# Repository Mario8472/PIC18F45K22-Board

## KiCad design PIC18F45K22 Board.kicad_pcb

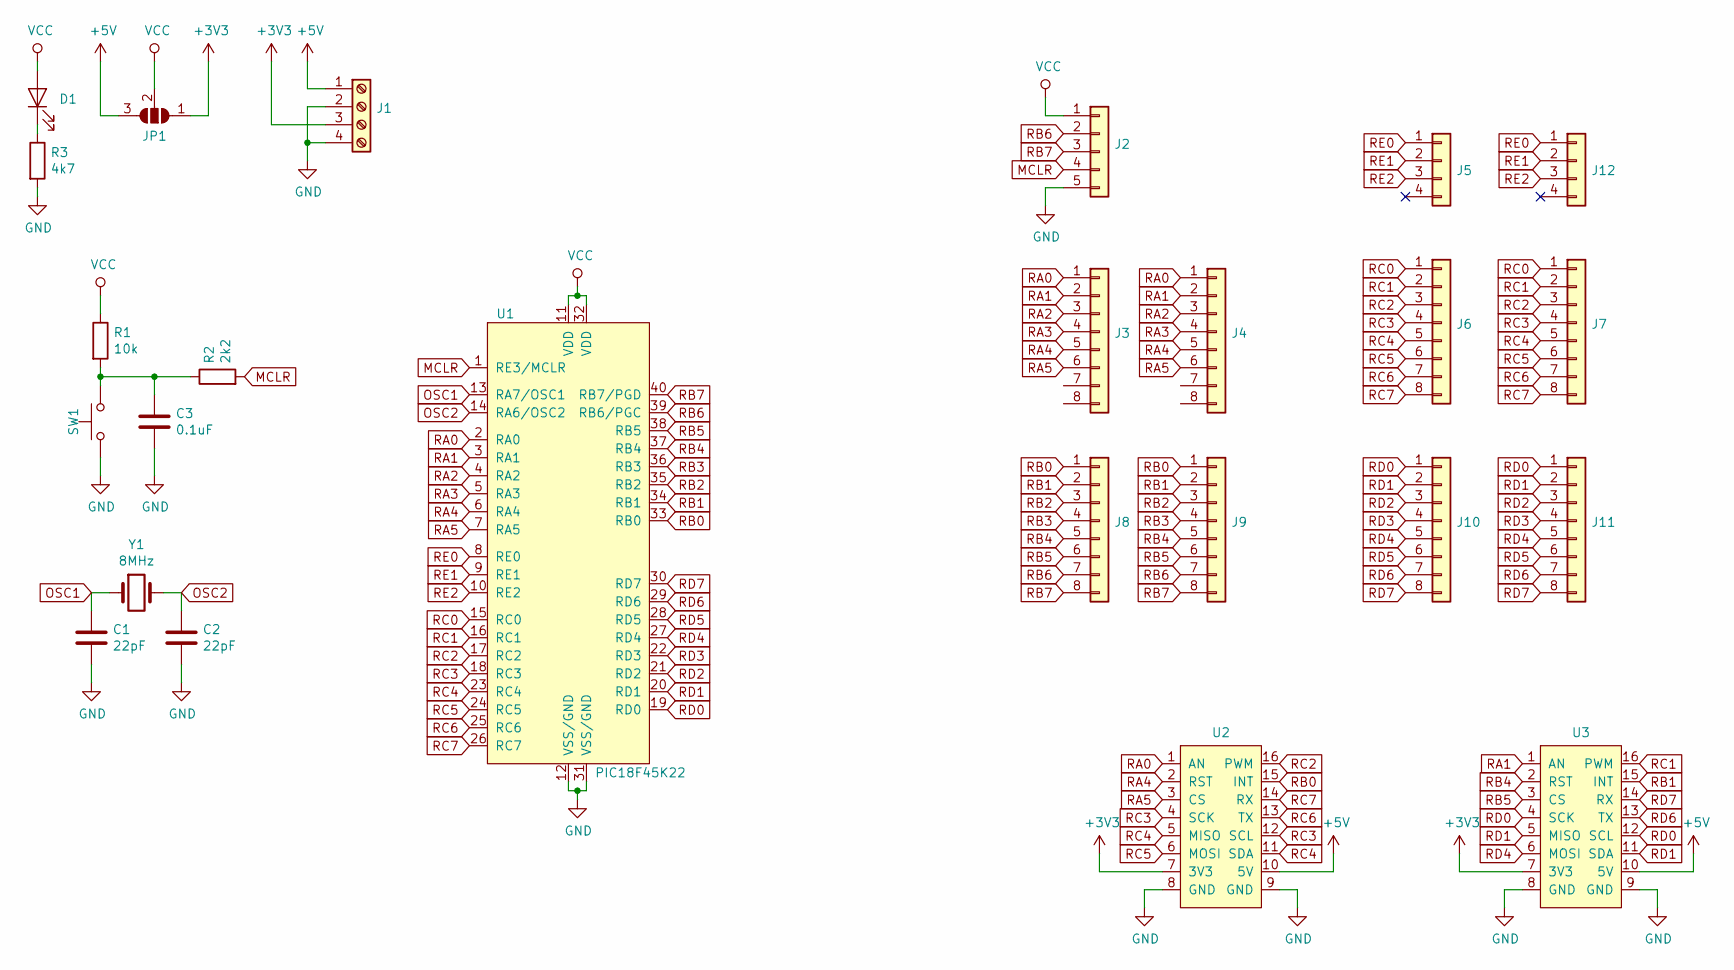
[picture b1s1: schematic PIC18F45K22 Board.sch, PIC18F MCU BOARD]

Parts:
C1, C2: 22pF; C_0805_2012Metric
C3: 0.1uF; C_0805_2012Metric
D1: PWR; LED_0805_2012Metric
J1: Screw_Terminal_01x04; PCB_Screw_Terminal_5.08_4ways
J2: Conn_01x05; PinHeader_1x05_P2.54mm_Vertical
J3, J4, J6, J7, J8, J9, J10, J11: Conn_01x08; PinHeader_1x08_P2.54mm_Vertical
J5, J12: Conn_01x04; PinHeader_1x04_P2.54mm_Vertical
JP1: SolderJumper_3_Open; Jumper_0805
R1: 10k; R_0805_2012Metric
R2: 2k2; R_0805_2012Metric
R3: 4k7; R_0805_2012Metric
SW1: SW_Push; TACTSWITCH6x6
U1: PIC18F45K22; DIP-40_W15.24mm_LongPads
U2, U3: mikroBUS_socket
Y1: 8MHz; Crystal_SMD_HC49-SD

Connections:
+3V3: J1.3, JP1.1 (A), U2.7 (3V3), U3.7 (3V3)
+5V: J1.1, JP1.3 (B), U2.10 (5V), U3.10 (5V)
GND: C1.2, C2.2, C3.2, J1.2, J1.4, J2.5, R3.2, SW1.1, U1.12 (VSS/GND), U1.31 (VSS/GND), U2.8 (GND), U2.9 (GND), U3.8 (GND), U3.9 (GND)
MCLR: J2.4, R2.2, U1.1 (RE3/MCLR)
unnamed: C3.1, R1.2, R2.1, SW1.2
unnamed: D1.1 (K), R3.1
OSC1: C1.1, U1.13 (RA7/OSC1), Y1.1
OSC2: C2.1, U1.14 (RA6/OSC2), Y1.2
RA0: J3.1, J4.1, U1.2 (RA0), U2.1 (AN)
RA1: J3.2, J4.2, U1.3 (RA1), U3.1 (AN)
RA2: J3.3, J4.3, U1.4 (RA2)
RA3: J3.4, J4.4, U1.5 (RA3)
RA4: J3.5, J4.5, U1.6 (RA4), U2.2 (RST)
RA5: J3.6, J4.6, U1.7 (RA5), U2.3 (CS)
RB0: J8.1, J9.1, U1.33 (RB0), U2.15 (INT)
RB1: J8.2, J9.2, U1.34 (RB1), U3.15 (INT)
RB2: J8.3, J9.3, U1.35 (RB2)
RB3: J8.4, J9.4, U1.36 (RB3)
RB4: J8.5, J9.5, U1.37 (RB4), U3.2 (RST)
RB5: J8.6, J9.6, U1.38 (RB5), U3.3 (CS)
RB6: J2.2, J8.7, J9.7, U1.39 (RB6/PGC)
RB7: J2.3, J8.8, J9.8, U1.40 (RB7/PGD)
RC0: J6.1, J7.1, U1.15 (RC0)
RC1: J6.2, J7.2, U1.16 (RC1), U3.16 (PWM)
RC2: J6.3, J7.3, U1.17 (RC2), U2.16 (PWM)
RC3: J6.4, J7.4, U1.18 (RC3), U2.4 (SCK), U2.12 (SCL)
RC4: J6.5, J7.5, U1.23 (RC4), U2.5 (MISO), U2.11 (SDA)
RC5: J6.6, J7.6, U1.24 (RC5), U2.6 (MOSI)
RC6: J6.7, J7.7, U1.25 (RC6), U2.13 (TX)
RC7: J6.8, J7.8, U1.26 (RC7), U2.14 (RX)
RD0: J10.1, J11.1, U1.19 (RD0), U3.4 (SCK), U3.12 (SCL)
RD1: J10.2, J11.2, U1.20 (RD1), U3.5 (MISO), U3.11 (SDA)
RD2: J10.3, J11.3, U1.21 (RD2)
RD3: J10.4, J11.4, U1.22 (RD3)
RD4: J10.5, J11.5, U1.27 (RD4), U3.6 (MOSI)
RD5: J10.6, J11.6, U1.28 (RD5)
RD6: J10.7, J11.7, U1.29 (RD6), U3.13 (TX)
RD7: J10.8, J11.8, U1.30 (RD7), U3.14 (RX)
RE0: J5.1, J12.1, U1.8 (RE0)
RE1: J5.2, J12.2, U1.9 (RE1)
RE2: J5.3, J12.3, U1.10 (RE2)
VCC: D1.2 (A), J2.1, JP1.2 (C), R1.1, U1.11 (VDD), U1.32 (VDD)

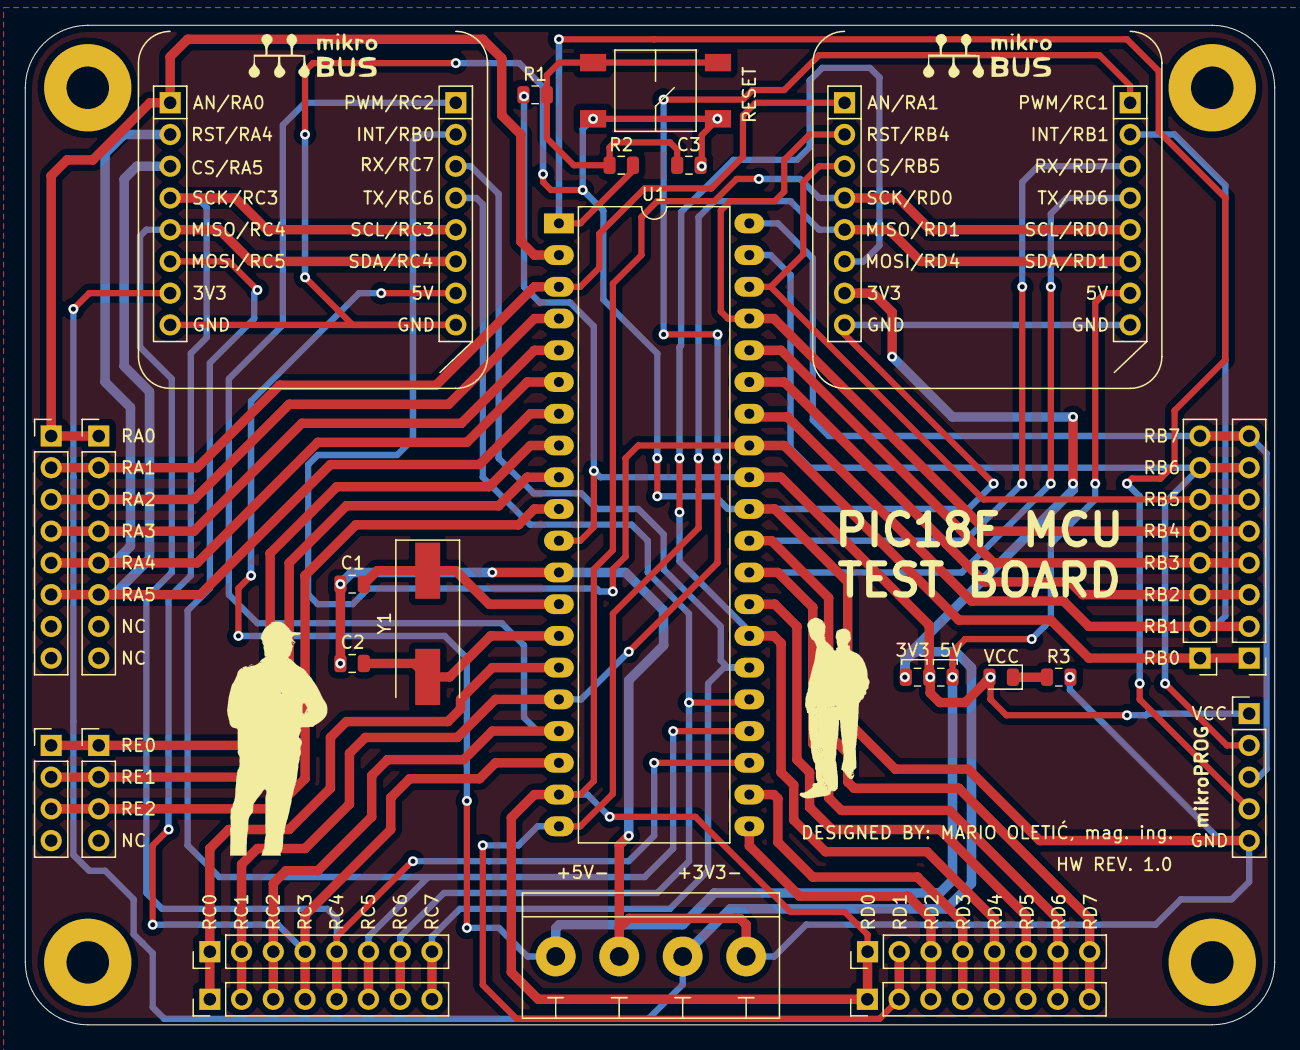
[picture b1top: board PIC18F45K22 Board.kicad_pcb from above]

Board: 2 copper layers, 100.0 x 80.0 mm, 25 parts (0 on the bottom side), 42 nets.
